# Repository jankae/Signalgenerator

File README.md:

# Signalgenerator

## What is it?
A homemade RF signal generator with these features:
* Frequency range: 5MHz to 2.1GHz
* Amplitude range: approx. -40dbm to +15dbm (slightly frequency dependent)
* Modulation
  * AM
  * FM
    * Up to 12.5MHz frequency deviation
  * QAM
    * Up to 32 constellation points
    * Up to 33M samples per second
    * Up to 36 samples per symbol
    * Pulse-shaping and differential encoding
  * External I/Q inputs
    * AC/DC coupling
    * Up to +30dbm/10Vpk input
    * Up to 10MHz of bandwidth
* Spectral purity@+10dbm:
  * Harmonic:
    * f >= 150MHz: <-30dbc
    * f >= 10MHz: <-25dbc
    * f < 10MHz: <-15dbc
  * Non-harmonic:
    * <-50dbc (limited by noise floor for lower output power)
  * Phase noise:
    * <-80dbc/Hz@10kHz offset

## Why was it build?
* Gain experience with RF circuit design
* Unwilling to pay the price for commercial generators (of course this one can't compete with a commercial one but should be good enough for simple RF experiments)

## How does it work?
For a high level overview see the description of the [RF generation](Documentation/RF.md).
For the effect of RF shielding see [these](Documentation/Shielding.md) measurements.

## More Pictures:
The inside: (I reused the frontpanel PCB from [this](https://github.com/jankae/battery-sim) project)

The external modulation input PCB:

The main RF board:

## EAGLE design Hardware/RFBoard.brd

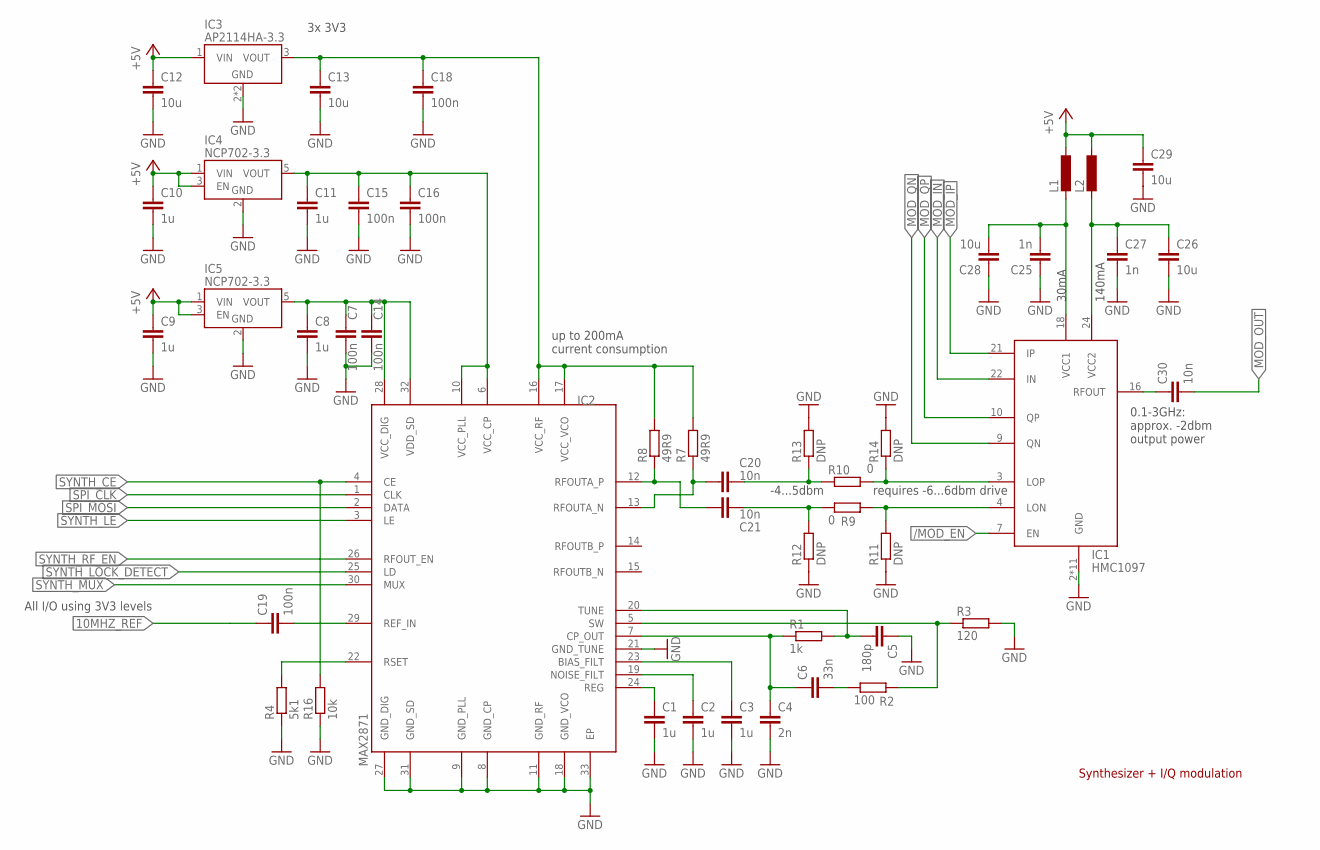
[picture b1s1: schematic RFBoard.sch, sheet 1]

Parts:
C1, C2, C3, C8, C9, C10, C11: 1u; C0603
C4: 2n; C0603
C5: 180p; C0603
C6: 33n; C0603
C7, C14, C15, C16, C18, C19: 100n; C0603
C12, C13, C26, C28, C29: 10u; C1206
C20, C21, C30: 10n; C0603
C25, C27: 1n; C0603
IC1: HMC1097; QFN50P400X400X100-25T280
IC2: MAX2871; QFN50P500X500X80-33T310
IC3: AP2114HA-3.3; SOT230P700X180-4
IC4, IC5: NCP702-3.3; SOT95P240X110-5
L1, L2: L-EUL2012C; L2012C
R1: 1k; R0603
R2: 100; R0603
R3: 120; R0603
R4: 5k1; R0603
R7, R8: 49R9; R0603
R9, R10: 0; R0603
R11, R12, R13, R14: DNP; R0603
R16: 10k; R0603

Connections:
10MHZ_REF: C19.1; also elsewhere on the board
+5V: C9.1, C10.1, C12.1, C29.1, IC3.1 (VIN), IC4.1 (VIN), IC4.3 (EN), IC5.1 (VIN), IC5.3 (EN), L1.1, L2.1; also elsewhere on the board
/MOD_EN: IC1.7 (EN); also elsewhere on the board
GND: C1.2, C2.2, C3.2, C4.2, C5.1, C7.2, C8.2, C9.2, C10.2, C11.2, C12.2, C13.2, C14.2, C15.2, C16.2, C18.2, C25.1, C26.2, C27.2, C28.1, C29.2, IC1.2 (GND), IC1.5 (GND), IC1.8 (GND), IC1.11 (GND), IC1.12 (GND), IC1.14 (GND), IC1.17 (GND), IC1.19 (GND), IC1.20 (GND), IC1.23 (GND), IC1.25 (GND), IC2.8 (GND_CP), IC2.9 (GND_PLL), IC2.11 (GND_RF), IC2.18 (GND_VCO), IC2.21 (GND_TUNE), IC2.27 (GND_DIG), IC2.31 (GND_SD), IC2.33 (EP), IC3.2 (GND), IC3.4 (GND), IC4.2 (GND), IC5.2 (GND), R3.2, R4.1, R11.1, R12.1, R13.2, R14.2, R16.1; also elsewhere on the board
MOD_IN: IC1.22 (IN); also elsewhere on the board
MOD_IP: IC1.21 (IP); also elsewhere on the board
MOD_OUT: C30.2; also elsewhere on the board
MOD_QN: IC1.9 (QN); also elsewhere on the board
MOD_QP: IC1.10 (QP); also elsewhere on the board
unnamed: C5.2, IC2.20 (TUNE), R1.2
unnamed: C4.1, C6.1, IC2.7 (CP_OUT), R1.1
unnamed: C1.1, IC2.24 (REG)
unnamed: C2.1, IC2.19 (NOISE_FILT)
unnamed: C3.1, IC2.23 (BIAS_FILT)
unnamed: C6.2, R2.1
unnamed: IC2.5 (SW), R2.2, R3.1
unnamed: IC2.22 (RSET), R4.2
unnamed: C19.2, IC2.29 (REF_IN)
unnamed: C13.1, C18.1, IC2.16 (VCC_RF), IC2.17 (VCC_VCO), IC3.3 (VOUT), R7.2, R8.2
unnamed: C11.1, C15.1, C16.1, IC2.6 (VCC_CP), IC2.10 (VCC_PLL), IC4.5 (VOUT)
unnamed: C20.1, IC2.13 (RFOUTA_N), R7.1
unnamed: C7.1, C8.1, C14.1, IC2.28 (VCC_DIG), IC2.32 (VDD_SD), IC5.5 (VOUT)
unnamed: C21.1, IC2.12 (RFOUTA_P), R8.1
unnamed: C20.2, R10.1, R13.1
unnamed: C21.2, R9.1, R12.2
unnamed: IC1.3 (LOP), R10.2, R14.1
unnamed: IC1.4 (LON), R9.2, R11.2
unnamed: C30.1, IC1.16 (RFOUT)
SPI_CLK: IC2.1 (CLK); also elsewhere on the board
SPI_MOSI: IC2.2 (DATA); also elsewhere on the board
SYNTH_CE: IC2.4 (CE), R16.2; also elsewhere on the board
SYNTH_LE: IC2.3 (LE); also elsewhere on the board
SYNTH_LOCK_DETECT: IC2.25 (LD); also elsewhere on the board
SYNTH_MUX: IC2.30 (MUX); also elsewhere on the board
SYNTH_RF_EN: IC2.26 (RFOUT_EN); also elsewhere on the board
VDD: C25.2, C28.2, IC1.18 (VCC1), L1.2
VDD1: C26.1, C27.1, IC1.24 (VCC2), L2.2

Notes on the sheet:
up to 200mA current consumption
All I/O using 3V3 levels
30mA
140mA
-4...5dbm
requires -6...6dbm drive
0.1-3GHz: approx. -2dbm output power
3x 3V3
Synthesizer + I/Q modulation

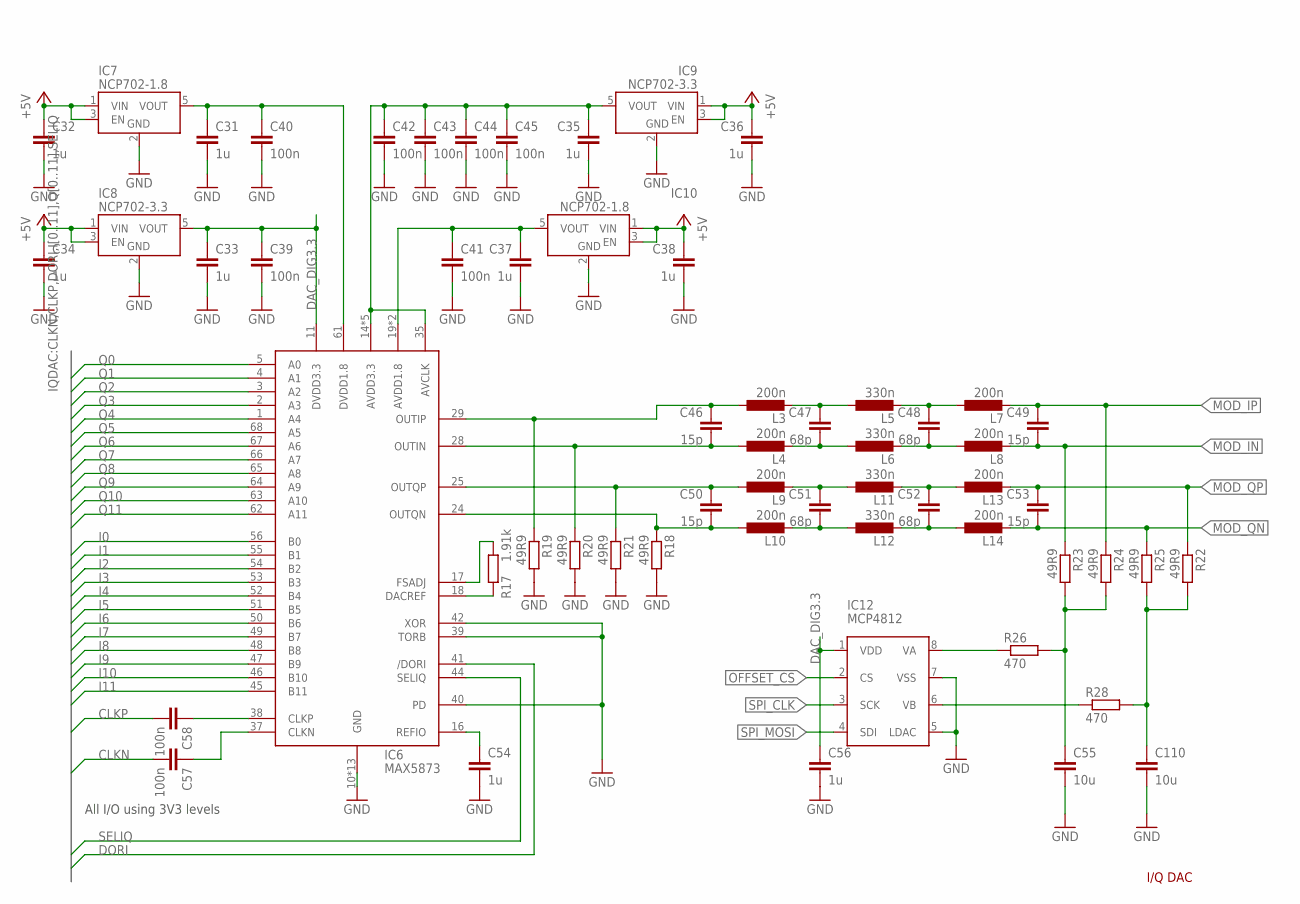
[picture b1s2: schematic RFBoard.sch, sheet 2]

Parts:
C31, C32, C33, C34, C35, C36, C37, C38, C54, C56: 1u; C0603
C39, C40, C41, C42, C43, C44, C45, C57, C58: 100n; C0603
C46, C49, C50, C53: 15p; C0603
C47, C48, C51, C52: 68p; C0603
C55, C110: 10u; C0603
IC6: MAX5873; QFN50P1000X1000X100-69T770
IC7, IC10: NCP702-1.8; SOT95P240X110-5
IC8, IC9: NCP702-3.3; SOT95P240X110-5
IC12: MCP4812; SO08
L3, L4, L7, L8, L9, L10, L13, L14: 200n; R0603
L5, L6, L11, L12: 330n; R0603
R17: 1.91k; R0603
R18, R19, R20, R21, R22, R23, R24, R25: 49R9; R0603
R26, R28: 470; R0603

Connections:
+5V: C32.1, C34.1, C36.1, C38.1, IC7.1 (VIN), IC7.3 (EN), IC8.1 (VIN), IC8.3 (EN), IC9.1 (VIN), IC9.3 (EN), IC10.1 (VIN), IC10.3 (EN); also elsewhere on the board
CLKN: C57.2; also elsewhere on the board
CLKP: C58.2; also elsewhere on the board
DAC_DIG3.3: C33.1, C39.1, C56.1, IC6.11 (DVDD3.3), IC8.5 (VOUT), IC12.1 (VDD)
DORI: IC6.41 (/DORI); also elsewhere on the board
GND: C31.2, C32.2, C33.2, C34.2, C35.2, C36.2, C37.2, C38.2, C39.2, C40.2, C41.2, C42.2, C43.2, C44.2, C45.2, C54.2, C55.2, C56.2, C110.2, IC6.10 (GND), IC6.12 (GND), IC6.13 (GND), IC6.15 (GND), IC6.20 (GND), IC6.23 (GND), IC6.26 (GND), IC6.27 (GND), IC6.30 (GND), IC6.33 (GND), IC6.36 (GND), IC6.39 (TORB), IC6.40 (PD), IC6.42 (XOR), IC6.43 (GND), IC6.69 (GND), IC7.2 (GND), IC8.2 (GND), IC9.2 (GND), IC10.2 (GND), IC12.5 (LDAC), IC12.7 (VSS), R18.2, R19.2, R20.2, R21.2; also elsewhere on the board
I0: IC6.56 (B0); also elsewhere on the board
I1: IC6.55 (B1); also elsewhere on the board
I2: IC6.54 (B2); also elsewhere on the board
I3: IC6.53 (B3); also elsewhere on the board
I4: IC6.52 (B4); also elsewhere on the board
I5: IC6.51 (B5); also elsewhere on the board
I6: IC6.50 (B6); also elsewhere on the board
I7: IC6.49 (B7); also elsewhere on the board
I8: IC6.48 (B8); also elsewhere on the board
I9: IC6.47 (B9); also elsewhere on the board
I10: IC6.46 (B10); also elsewhere on the board
I11: IC6.45 (B11); also elsewhere on the board
MOD_IN: C49.2, L8.2, R23.1; also elsewhere on the board
MOD_IP: C49.1, L7.2, R24.1; also elsewhere on the board
MOD_QN: C53.2, L14.2, R25.1; also elsewhere on the board
MOD_QP: C53.1, L13.2, R22.1; also elsewhere on the board
unnamed: C31.1, C40.1, IC6.61 (DVDD1.8), IC7.5 (VOUT)
unnamed: C58.1, IC6.38 (CLKP)
unnamed: C35.1, C42.1, C43.1, C44.1, C45.1, IC6.14 (AVDD3.3), IC6.21 (AVDD3.3), IC6.22 (AVDD3.3), IC6.31 (AVDD3.3), IC6.32 (AVDD3.3), IC6.35 (AVCLK), IC9.5 (VOUT)
unnamed: C37.1, C41.1, IC6.19 (AVDD1.8), IC6.34 (AVDD1.8), IC10.5 (VOUT)
unnamed: IC6.18 (DACREF), R17.2
unnamed: IC6.17 (FSADJ), R17.1
unnamed: C55.1, R23.2, R24.2, R26.2
unnamed: C110.1, R22.2, R25.2, R28.2
unnamed: C46.2, IC6.28 (OUTIN), L4.1, R20.1
unnamed: C46.1, IC6.29 (OUTIP), L3.1, R19.1
unnamed: C47.2, L4.2, L6.1
unnamed: C48.2, L6.2, L8.1
unnamed: C47.1, L3.2, L5.1
unnamed: C48.1, L5.2, L7.1
unnamed: C54.1, IC6.16 (REFIO)
unnamed: IC12.8 (VA), R26.1
unnamed: C50.2, IC6.24 (OUTQN), L10.1, R18.1
unnamed: C50.1, IC6.25 (OUTQP), L9.1, R21.1
unnamed: C51.2, L10.2, L12.1
unnamed: C52.2, L12.2, L14.1
unnamed: C51.1, L9.2, L11.1
unnamed: C52.1, L11.2, L13.1
unnamed: C57.1, IC6.37 (CLKN)
unnamed: IC12.6 (VB), R28.1
OFFSET_CS: IC12.2 (CS); also elsewhere on the board
Q0: IC6.5 (A0); also elsewhere on the board
Q1: IC6.4 (A1); also elsewhere on the board
Q2: IC6.3 (A2); also elsewhere on the board
Q3: IC6.2 (A3); also elsewhere on the board
Q4: IC6.1 (A4); also elsewhere on the board
Q5: IC6.68 (A5); also elsewhere on the board
Q6: IC6.67 (A6); also elsewhere on the board
Q7: IC6.66 (A7); also elsewhere on the board
Q8: IC6.65 (A8); also elsewhere on the board
Q9: IC6.64 (A9); also elsewhere on the board
Q10: IC6.63 (A10); also elsewhere on the board
Q11: IC6.62 (A11); also elsewhere on the board
SELIQ: IC6.44 (SELIQ); also elsewhere on the board
SPI_CLK: IC12.3 (SCK); also elsewhere on the board
SPI_MOSI: IC12.4 (SDI); also elsewhere on the board

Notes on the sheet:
I/Q DAC
All I/O using 3V3 levels

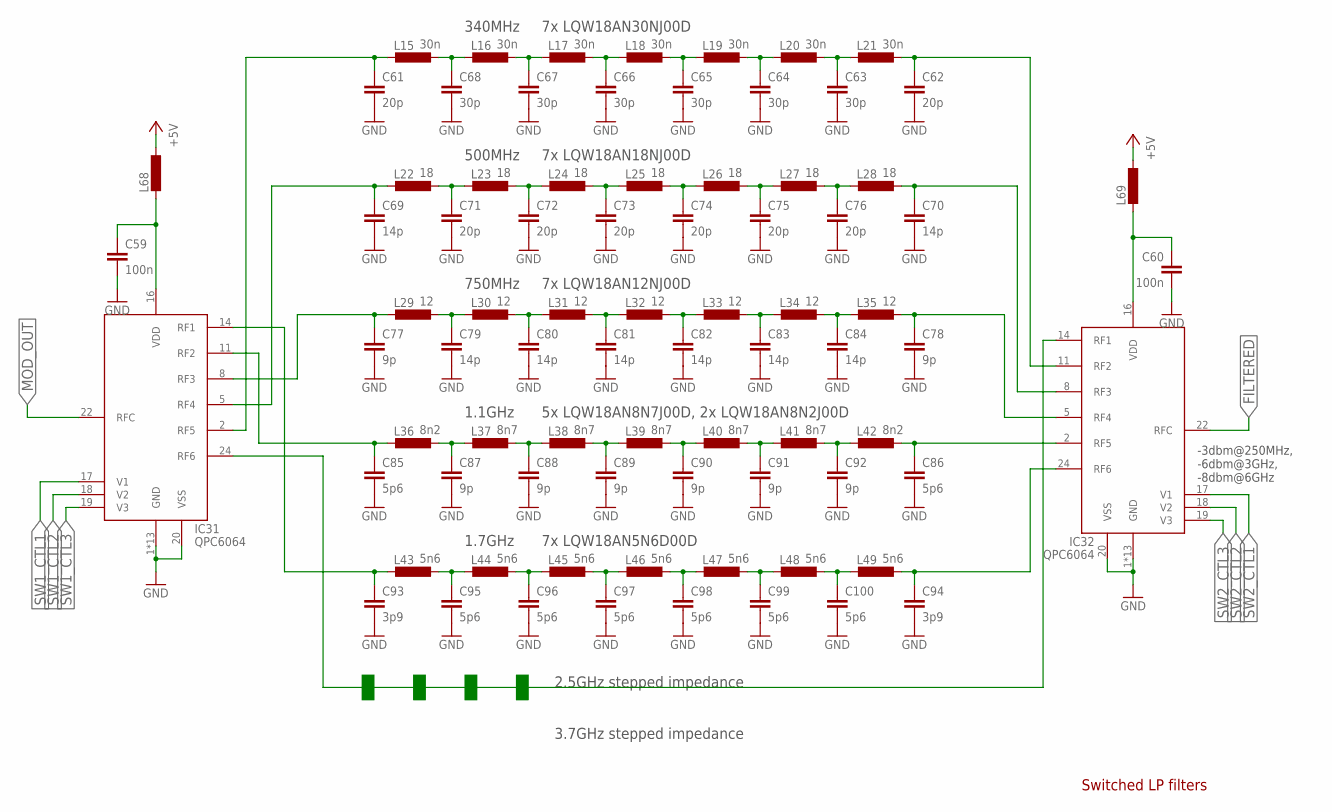
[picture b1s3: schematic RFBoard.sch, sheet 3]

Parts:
C59, C60: 100n; C0603
C61, C62, C71, C72, C73, C74, C75, C76: 20p; C0603
C63, C64, C65, C66, C67, C68: 30p; C0603
C69, C70, C79, C80, C81, C82, C83, C84: 14p; C0603
C77, C78, C87, C88, C89, C90, C91, C92: 9p; C0603
C85, C86, C95, C96, C97, C98, C99, C100: 5p6; C0603
C93, C94: 3p9; C0603
IC31, IC32: QPC6064; QFN50P400X400X75-25T270
L15, L16, L17, L18, L19, L20, L21: 30n; R0603
L22, L23, L24, L25, L26, L27, L28: 18; R0603
L29, L30, L31, L32, L33, L34, L35: 12; R0603
L36, L42: 8n2; R0603
L37, L38, L39, L40, L41: 8n7; R0603
L43, L44, L45, L46, L47, L48, L49: 5n6; R0603
L68, L69: L-EUL2012C; L2012C

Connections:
+5V: L68.1, L69.1; also elsewhere on the board
FILTERED: IC32.22 (RFC); also elsewhere on the board
GND: C59.2, C60.2, C61.2, C62.2, C63.2, C64.2, C65.2, C66.2, C67.2, C68.2, C69.2, C70.2, C71.2, C72.2, C73.2, C74.2, C75.2, C76.2, C77.2, C78.2, C79.2, C80.2, C81.2, C82.2, C83.2, C84.2, C85.2, C86.2, C87.2, C88.2, C89.2, C90.2, C91.2, C92.2, C93.2, C94.2, C95.2, C96.2, C97.2, C98.2, C99.2, C100.2, IC31.1 (GND), IC31.3 (GND), IC31.4 (GND), IC31.6 (GND), IC31.7 (GND), IC31.9 (GND), IC31.10 (GND), IC31.12 (GND), IC31.13 (GND), IC31.15 (GND), IC31.20 (VSS), IC31.21 (GND), IC31.23 (GND), IC31.25 (GND), IC32.1 (GND), IC32.3 (GND), IC32.4 (GND), IC32.6 (GND), IC32.7 (GND), IC32.9 (GND), IC32.10 (GND), IC32.12 (GND), IC32.13 (GND), IC32.15 (GND), IC32.20 (VSS), IC32.21 (GND), IC32.23 (GND), IC32.25 (GND); also elsewhere on the board
MOD_OUT: IC31.22 (RFC); also elsewhere on the board
unnamed: C68.1, L15.1, L16.2
unnamed: C67.1, L16.1, L17.2
unnamed: C66.1, L17.1, L18.2
unnamed: C65.1, L18.1, L19.2
unnamed: C64.1, L19.1, L20.2
unnamed: C63.1, L20.1, L21.2
unnamed: C61.1, IC31.2 (RF5), L15.2
unnamed: C62.1, IC32.11 (RF2), L21.1
unnamed: C71.1, L22.1, L23.2
unnamed: C72.1, L23.1, L24.2
unnamed: C73.1, L24.1, L25.2
unnamed: C74.1, L25.1, L26.2
unnamed: C75.1, L26.1, L27.2
unnamed: C76.1, L27.1, L28.2
unnamed: C69.1, IC31.5 (RF4), L22.2
unnamed: C79.1, L29.1, L30.2
unnamed: C80.1, L30.1, L31.2
unnamed: C81.1, L31.1, L32.2
unnamed: C82.1, L32.1, L33.2
unnamed: C83.1, L33.1, L34.2
unnamed: C84.1, L34.1, L35.2
unnamed: C78.1, IC32.5 (RF4), L35.1
unnamed: C87.1, L36.1, L37.2
unnamed: C88.1, L37.1, L38.2
unnamed: C89.1, L38.1, L39.2
unnamed: C90.1, L39.1, L40.2
unnamed: C91.1, L40.1, L41.2
unnamed: C92.1, L41.1, L42.2
unnamed: C85.1, IC31.11 (RF2), L36.2
unnamed: C86.1, IC32.2 (RF5), L42.1
unnamed: C95.1, L43.1, L44.2
unnamed: C96.1, L44.1, L45.2
unnamed: C97.1, L45.1, L46.2
unnamed: C98.1, L46.1, L47.2
unnamed: C99.1, L47.1, L48.2
unnamed: C100.1, L48.1, L49.2
unnamed: C93.1, IC31.14 (RF1), L43.2
unnamed: C94.1, IC32.24 (RF6), L49.1
unnamed: C77.1, IC31.8 (RF3), L29.2
unnamed: C70.1, IC32.8 (RF3), L28.1
STEPPED25: IC31.24 (RF6), IC32.14 (RF1)
SW1_CTL1: IC31.17 (V1); also elsewhere on the board
SW1_CTL2: IC31.18 (V2); also elsewhere on the board
SW1_CTL3: IC31.19 (V3); also elsewhere on the board
SW2_CTL1: IC32.17 (V1); also elsewhere on the board
SW2_CTL2: IC32.18 (V2); also elsewhere on the board
SW2_CTL3: IC32.19 (V3); also elsewhere on the board
SWITCHES_VCC: C60.1, IC32.16 (VDD), L69.2
VDD2: C59.1, IC31.16 (VDD), L68.2

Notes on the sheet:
Switched LP filters
7x LQW18AN30NJ00D
340MHz
7x LQW18AN18NJ00D
500MHz
7x LQW18AN12NJ00D
750MHz
5x LQW18AN8N7J00D, 2x LQW18AN8N2J00D
1.1GHz
7x LQW18AN5N6D00D
1.7GHz
2.5GHz stepped impedance
3.7GHz stepped impedance
-3dbm@250MHz, -6dbm@3GHz, -8dbm@6GHz

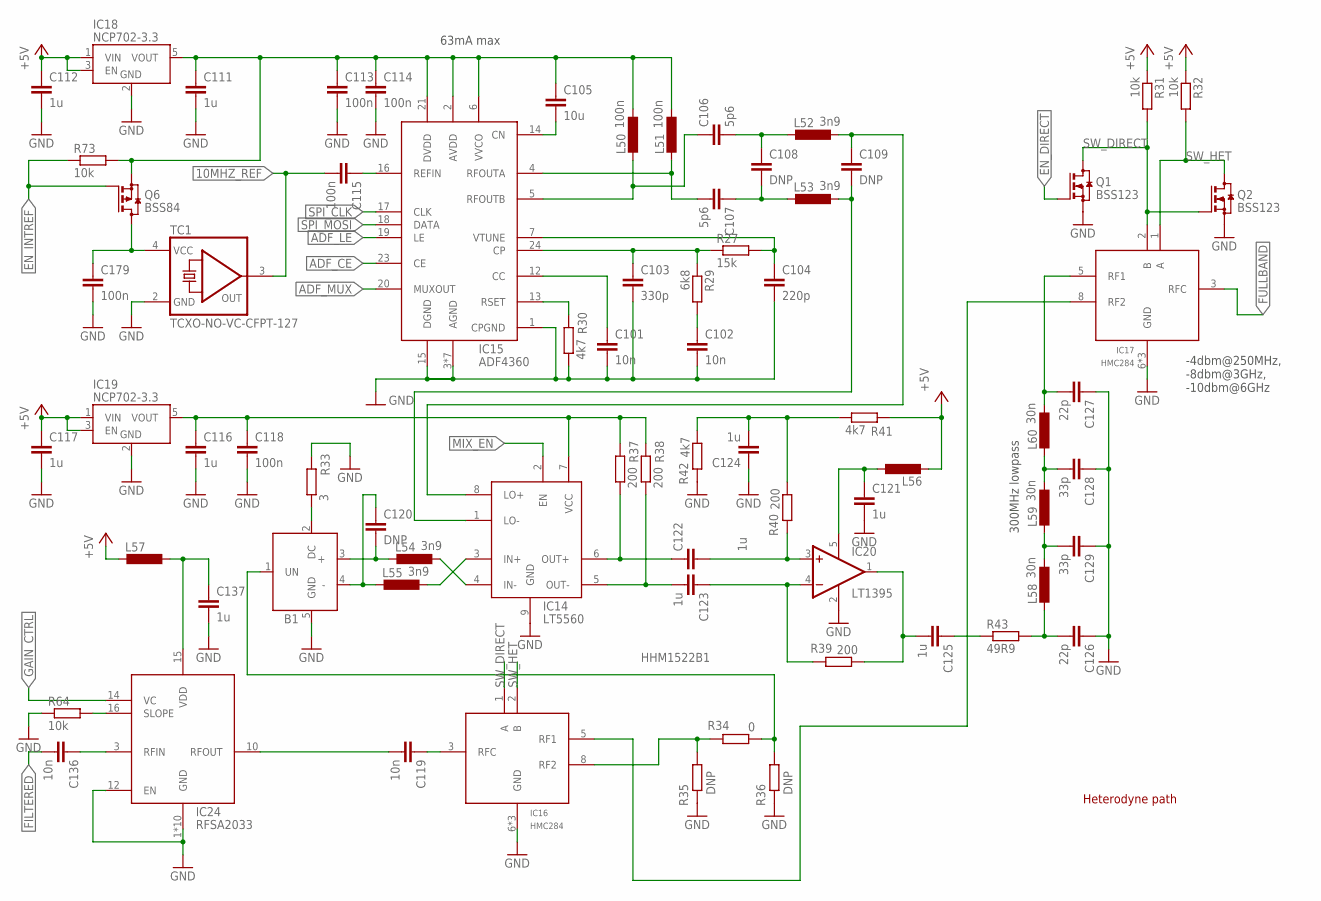
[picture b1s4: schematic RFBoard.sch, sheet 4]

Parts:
B1: HHM1522B1; INDCAF65P200X125X95-6
C101, C102, C119, C136: 10n; C0603
C103: 330p; C0603
C104: 220p; C0603
C105: 10u; C0603
C106, C107: 5p6; C0603
C108, C109, C120: DNP; C0603
C111, C112, C116, C117, C121, C122, C123, C124, C125, C137: 1u; C0603
C113, C114, C115, C118, C179: 100n; C0603
C126, C127: 22p; C0603
C128, C129: 33p; C0603
IC14: LT5560; SON50P300X300X80-9T165X238
IC15: ADF4360; QFN50P400X400X80-25T230
IC16, IC17: HMC284; MSOP08
IC18, IC19: NCP702-3.3; SOT95P240X110-5
IC20: LT1395; SOT23-5
IC24: RFSA2033; QFN50P300X300X85-17T170
L50, L51: 100n; R0603
L52, L53, L54, L55: 3n9; R0603
L56, L57: L-EUL2012C; L2012C
L58, L59, L60: 30n; R0603
Q1, Q2: BSS123; SOT23
Q6: BSS84; SOT23
R27: 15k; R0603
R29: 6k8; R0603
R30, R41, R42: 4k7; R0603
R31, R32, R64, R73: 10k; R0603
R33: 3; R0603
R34: 0; R0603
R35, R36: DNP; R0603
R37, R38, R39, R40: 200; R0603
R43: 49R9; R0603
TC1: TCXO-NO-VC-CFPT-127; 5.0X3.2-TCXO

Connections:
10MHZ_REF: C115.2, TC1.3 (OUT); also elsewhere on the board
+5V: C112.1, C117.1, IC18.1 (VIN), IC18.3 (EN), IC19.1 (VIN), IC19.3 (EN), L56.2, L57.2, R31.1, R32.1, R41.2; also elsewhere on the board
ADF_CE: IC15.23 (CE); also elsewhere on the board
ADF_LE: IC15.19 (LE); also elsewhere on the board
ADF_MUX: IC15.20 (MUXOUT); also elsewhere on the board
DAC_DIG3.2: C116.1, C118.1, IC14.7 (VCC), IC19.5 (VOUT), R37.2, R38.2
EN_DIRECT: Q1.1 (G); also elsewhere on the board
EN_INTREF: Q6.1 (G), R73.1; also elsewhere on the board
FILTERED: C136.2; also elsewhere on the board
FULLBAND: IC17.3 (RFC); also elsewhere on the board
GAIN_CTRL: IC24.14 (VC); also elsewhere on the board
GND: B1.5 (GND), C101.2, C102.2, C103.2, C104.2, C111.2, C112.2, C113.2, C114.2, C116.2, C117.2, C118.2, C121.2, C124.1, C126.1, C127.1, C128.1, C129.1, C137.2, C179.2, IC14.9 (GND), IC15.1 (CPGND), IC15.3 (AGND), IC15.8 (AGND), IC15.9 (AGND), IC15.10 (AGND), IC15.11 (AGND), IC15.15 (DGND), IC15.22 (AGND), IC15.25 (AGND), IC16.6 (GND), IC16.7 (GND), IC16.9 (GND), IC17.6 (GND), IC17.7 (GND), IC17.9 (GND), IC18.2 (GND), IC19.2 (GND), IC20.2 (V-), IC24.1 (GND), IC24.2 (GND), IC24.4 (GND), IC24.5 (GND), IC24.6 (GND), IC24.7 (GND), IC24.8 (GND), IC24.9 (GND), IC24.11 (GND), IC24.12 (EN), IC24.17 (GND), Q1.2 (S), Q2.2 (S), R30.1, R33.2, R35.2, R36.2, R42.2, R64.1, TC1.2 (GND); also elsewhere on the board
MIX_EN: IC14.2 (EN); also elsewhere on the board
unnamed: IC14.3 (IN+), L55.1
unnamed: IC14.4 (IN-), L54.1
unnamed: IC15.13 (RSET), R30.2
unnamed: C101.1, IC15.12 (CC)
unnamed: C102.1, R29.2
unnamed: C103.1, IC15.24 (CP), R27.1, R29.1
unnamed: C104.1, IC15.7 (VTUNE), R27.2
unnamed: C115.1, IC15.16 (REFIN)
unnamed: C105.2, IC15.14 (CN)
unnamed: C106.1, IC15.5 (RFOUTB), L50.2
unnamed: C107.2, IC15.4 (RFOUTA), L51.2
unnamed: C106.2, C108.1, L52.2
unnamed: C107.1, C108.2, L53.2
unnamed: C109.1, IC14.8 (LO+), L52.1
unnamed: C109.2, IC14.1 (LO-), L53.1
unnamed: C119.1, IC16.3 (RFC)
unnamed: B1.3 (+), C120.2, L54.2
unnamed: B1.4 (-), C120.1, L55.2
unnamed: IC16.5 (RF1), IC17.8 (RF2)
unnamed: IC16.8 (RF2), R34.2, R35.1
unnamed: B1.2 (DC), R33.1
unnamed: B1.1 (UN), R34.1, R36.1
unnamed: C121.1, IC20.5 (V+), L56.1
unnamed: C122.1, IC14.6 (OUT+), R37.1
unnamed: C123.2, IC14.5 (OUT-), R38.1
unnamed: C125.2, IC20.1 (OUT), R39.1
unnamed: C123.1, IC20.4 (-IN), R39.2
unnamed: C122.2, IC20.3 (+IN), R40.2
unnamed: C124.2, R40.1, R41.1, R42.1
unnamed: C125.1, R43.1
unnamed: C127.2, IC17.5 (RF1), L60.1
unnamed: C126.2, L58.2, R43.2
unnamed: C129.2, L58.1, L59.2
unnamed: C128.2, L59.1, L60.2
unnamed: C119.2, IC24.10 (RFOUT)
unnamed: C136.1, IC24.3 (RFIN)
unnamed: C137.1, IC24.15 (VDD), L57.1
unnamed: IC24.16 (SLOPE), R64.2
unnamed: C179.1, Q6.3 (D), TC1.4 (VCC)
PLL_DIG3: C105.1, C111.1, C113.1, C114.1, IC15.2 (AVDD), IC15.6 (VVCO), IC15.21 (DVDD), IC18.5 (VOUT), L50.1, L51.1, Q6.2 (S), R73.2
SPI_CLK: IC15.17 (CLK); also elsewhere on the board
SPI_MOSI: IC15.18 (DATA); also elsewhere on the board
SW_DIRECT: IC16.1 (A), IC17.2 (B), Q1.3 (D), Q2.1 (G), R31.2
SW_HET: IC16.2 (B), IC17.1 (A), Q2.3 (D), R32.2

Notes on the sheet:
Heterodyne path
-4dbm@250MHz, -8dbm@3GHz, -10dbm@6GHz
300MHz lowpass
63mA max

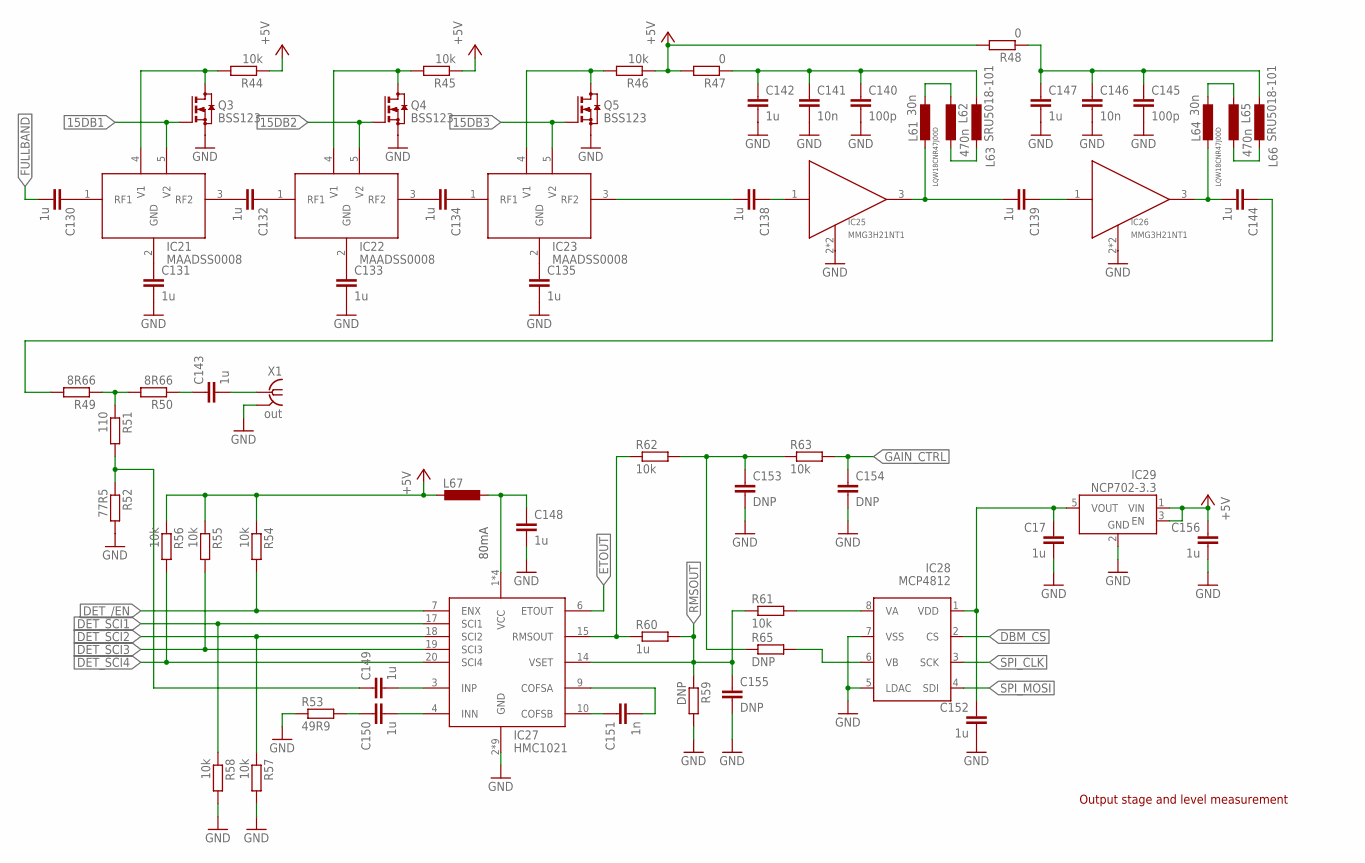
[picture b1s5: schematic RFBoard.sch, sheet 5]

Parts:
C17, C130, C131, C132, C133, C134, C135, C138, C139, C142, C143, C144, C147, C148, C149, C150, C152, C156: 1u; C0603
C140, C145: 100p; C0603
C141, C146: 10n; C0603
C151: 1n; C0603
C153, C154, C155: DNP; C0603
IC21, IC22, IC23: MAADSS0008; SOT95P280X110-5
IC25, IC26: MMG3H21NT1; SOT89
IC27: HMC1021; QFN50P400X400X100-25T270
IC28: MCP4812; SO08
IC29: NCP702-3.3; SOT95P240X110-5
L61, L64: 30n; R0603
L62, L65: 470n; R0603
L63, L66: SRU5018-101; SMD5018
L67: L-EUL2012C; L2012C
Q3, Q4, Q5: BSS123; SOT23
R44, R45, R46, R54, R55, R56, R57, R58, R61, R62, R63: 10k; R0603
R47, R48: 0; R0603
R49, R50: 8R66; R0603
R51: 110; R0603
R52: 77R5; R0603
R53: 49R9; R0603
R59, R65: DNP; R0603
R60: 1u; R0603
X1: out; J502-ND-142-0711-821/826

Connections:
15DB1: IC21.5 (V2), Q3.1 (G); also elsewhere on the board
15DB2: IC22.5 (V2), Q4.1 (G); also elsewhere on the board
15DB3: IC23.5 (V2), Q5.1 (G); also elsewhere on the board
+5V: C156.1, IC29.1 (VIN), IC29.3 (EN), L67.2, R44.1, R45.1, R46.1, R47.2, R48.2, R54.1, R55.1, R56.1; also elsewhere on the board
DBM_CS: IC28.2 (CS); also elsewhere on the board
DET_/EN: IC27.7 (ENX), R54.2; also elsewhere on the board
DET_SCI1: IC27.17 (SCI1), R58.1; also elsewhere on the board
DET_SCI2: IC27.18 (SCI2), R57.1; also elsewhere on the board
DET_SCI3: IC27.19 (SCI3), R55.2; also elsewhere on the board
DET_SCI4: IC27.20 (SCI4), R56.2; also elsewhere on the board
ETOUT: IC27.6 (ETOUT); also elsewhere on the board
FULLBAND: C130.2; also elsewhere on the board
GAIN_CTRL: C154.1, R63.2; also elsewhere on the board
GND: C17.2, C131.2, C133.2, C135.2, C140.2, C141.2, C142.2, C145.2, C146.2, C147.2, C148.2, C152.2, C153.2, C154.2, C155.2, C156.2, IC25.2 (GND), IC25.2@1 (GND), IC26.2 (GND), IC26.2@1 (GND), IC27.2 (GND), IC27.5 (GND), IC27.8 (GND), IC27.11 (GND), IC27.12 (GND), IC27.13 (GND), IC27.22 (GND), IC27.24 (GND), IC27.25 (GND), IC28.5 (LDAC), IC28.7 (VSS), IC29.2 (GND), Q3.2 (S), Q4.2 (S), Q5.2 (S), R52.2, R53.1, R57.2, R58.2, R59.2, X1.G@1 (2), X1.G@2 (2), X1.G@3 (2), X1.G@4 (2); also elsewhere on the board
unnamed: IC28.8 (VA), R61.2
unnamed: IC28.6 (VB), R65.2
unnamed: C131.1, IC21.2 (GND)
unnamed: C130.1, IC21.1 (RF1)
unnamed: C132.1, IC22.1 (RF1)
unnamed: IC21.4 (V1), Q3.3 (D), R44.2
unnamed: C133.1, IC22.2 (GND)
unnamed: IC22.4 (V1), Q4.3 (D), R45.2
unnamed: C134.1, IC23.1 (RF1)
unnamed: C135.1, IC23.2 (GND)
unnamed: IC23.4 (V1), Q5.3 (D), R46.2
unnamed: C134.2, IC22.3 (RF2)
unnamed: C132.2, IC21.3 (RF2)
unnamed: C139.2, IC25.3 (OUT), L61.2
unnamed: C138.1, IC25.1 (IN)
unnamed: L61.1, L62.2
unnamed: L62.1, L63.P$3 (2)
unnamed: C144.2, IC26.3 (OUT), L64.2
unnamed: C140.1, C141.1, C142.1, L63.P$1 (1), R47.1
unnamed: C139.1, IC26.1 (IN)
unnamed: C145.1, C146.1, C147.1, L66.P$1 (1), R48.1
unnamed: L64.1, L65.2
unnamed: L65.1, L66.P$3 (2)
unnamed: C138.2, IC23.3 (RF2)
unnamed: C144.1, R49.2
unnamed: R49.1, R50.2, R51.1
unnamed: C143.1, R50.1
unnamed: C149.1, R51.2, R52.1
unnamed: C143.2, X1.1
unnamed: C148.1, IC27.1 (VCC), IC27.16 (VCC), IC27.21 (VCC), IC27.23 (VCC), L67.1
unnamed: C149.2, IC27.3 (INP)
unnamed: C150.2, IC27.4 (INN)
unnamed: C153.1, R62.2, R63.1, R65.1
unnamed: C150.1, R53.2
unnamed: C151.1, IC27.10 (COFSB)
unnamed: C151.2, IC27.9 (COFSA)
unnamed: IC27.15 (RMSOUT), R60.1, R62.1
RMSOUT: C155.1, IC27.14 (VSET), R59.1, R60.2, R61.1; also elsewhere on the board
SETDAC_VCC: C17.1, C152.1, IC28.1 (VDD), IC29.5 (VOUT)
SPI_CLK: IC28.3 (SCK); also elsewhere on the board
SPI_MOSI: IC28.4 (SDI); also elsewhere on the board

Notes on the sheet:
LQW18CNR47J00D
80mA
Output stage and level measurement

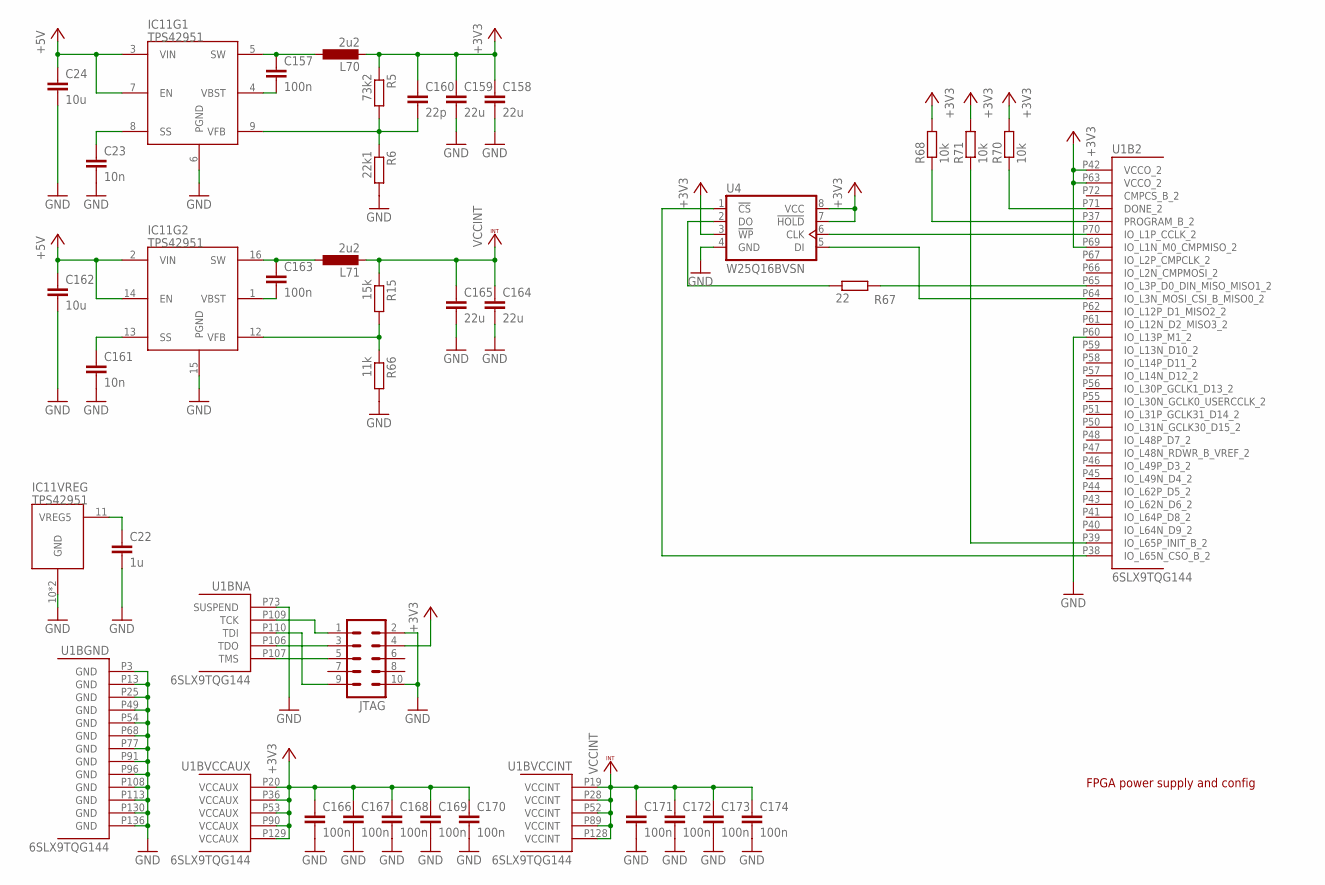
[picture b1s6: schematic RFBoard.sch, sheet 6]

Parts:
C22: 1u; C0603
C23, C161: 10n; C0603
C24, C162: 10u; C1206
C157, C163, C166, C167, C168, C169, C170, C171, C172, C173, C174: 100n; C0603
C158, C159, C164, C165: 22u; C1206
C160: 22p; C0603
IC11: TPS42951; QFN65P400X400X100-17T270
JTAG: ML10
L70, L71: 2u2; SRN5040
R5: 73k2; R0603
R6: 22k1; R0603
R15: 15k; R0603
R66: 11k; R0603
R67: 22; R0603
R68, R70, R71: 10k; R0603
U1: 6SLX9TQG144; TQ144
U4: W25Q16BVSN; SO08

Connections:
+3V3: C158.1, C159.1, C160.1, C166.1, C167.1, C168.1, C169.1, C170.1, JTAG.4, L70.P$2 (2), R5.1, R68.2, R70.2, R71.2, U1.P20 (VCCAUX), U1.P36 (VCCAUX), U1.P42 (VCCO_2), U1.P53 (VCCAUX), U1.P63 (VCCO_2), U1.P69 (IO_L1N_M0_CMPMISO_2), U1.P90 (VCCAUX), U1.P129 (VCCAUX), U4.3 (!WP!), U4.7 (!HOLD!), U4.8 (VCC); also elsewhere on the board
+5V: C24.1, C162.1, IC11.2 (VIN), IC11.3 (VIN), IC11.7 (EN), IC11.14 (EN); also elsewhere on the board
FLACH_MOSI: U1.P64 (IO_L3N_MOSI_CSI_B_MISO0_2), U4.5 (DI)
FLASH_CLK: U1.P70 (IO_L1P_CCLK_2), U4.6 (CLK)
FLASH_CS: U1.P38 (IO_L65N_CSO_B_2), U4.1 (!CS!)
FLASH_MISO: R67.1, U4.2 (DO)
GND: C22.2, C23.2, C24.2, C158.2, C159.2, C161.2, C162.2, C164.2, C165.2, C166.2, C167.2, C168.2, C169.2, C170.2, C171.2, C172.2, C173.2, C174.2, IC11.6 (PGND), IC11.10 (GND), IC11.15 (PGND), IC11.17 (GND), JTAG.2, JTAG.10, R6.2, R66.2, U1.P3 (GND), U1.P13 (GND), U1.P25 (GND), U1.P49 (GND), U1.P54 (GND), U1.P60 (IO_L13P_M1_2), U1.P68 (GND), U1.P73 (SUSPEND), U1.P77 (GND), U1.P91 (GND), U1.P96 (GND), U1.P108 (GND), U1.P113 (GND), U1.P130 (GND), U1.P136 (GND), U4.4 (GND); also elsewhere on the board
unnamed: JTAG.3, U1.P106 (TDO)
unnamed: JTAG.5, U1.P107 (TMS)
unnamed: JTAG.9, U1.P110 (TDI)
unnamed: JTAG.1, U1.P109 (TCK)
unnamed: C22.1, IC11.11 (VREG5)
unnamed: C23.1, IC11.8 (SS)
unnamed: C160.2, IC11.9 (VFB), R5.2, R6.1
unnamed: C161.1, IC11.13 (SS)
unnamed: C157.1, IC11.5 (SW), L70.P$1 (1)
unnamed: C157.2, IC11.4 (VBST)
unnamed: IC11.12 (VFB), R15.2, R66.1
unnamed: C163.1, IC11.16 (SW), L71.P$1 (1)
unnamed: C163.2, IC11.1 (VBST)
unnamed: R67.2, U1.P65 (IO_L3P_D0_DIN_MISO_MISO1_2)
unnamed: R70.1, U1.P71 (DONE_2)
unnamed: R68.1, U1.P37 (PROGRAM_B_2)
unnamed: R71.1, U1.P39 (IO_L65P_INIT_B_2)
VCCINT: C164.1, C165.1, C171.1, C172.1, C173.1, C174.1, L71.P$2 (2), R15.1, U1.P19 (VCCINT), U1.P28 (VCCINT), U1.P52 (VCCINT), U1.P89 (VCCINT), U1.P128 (VCCINT); also elsewhere on the board

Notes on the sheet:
FPGA power supply and config

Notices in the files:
parts and their libraries:
memory-winbond: Copyright (C) 2010, Bob Starr
